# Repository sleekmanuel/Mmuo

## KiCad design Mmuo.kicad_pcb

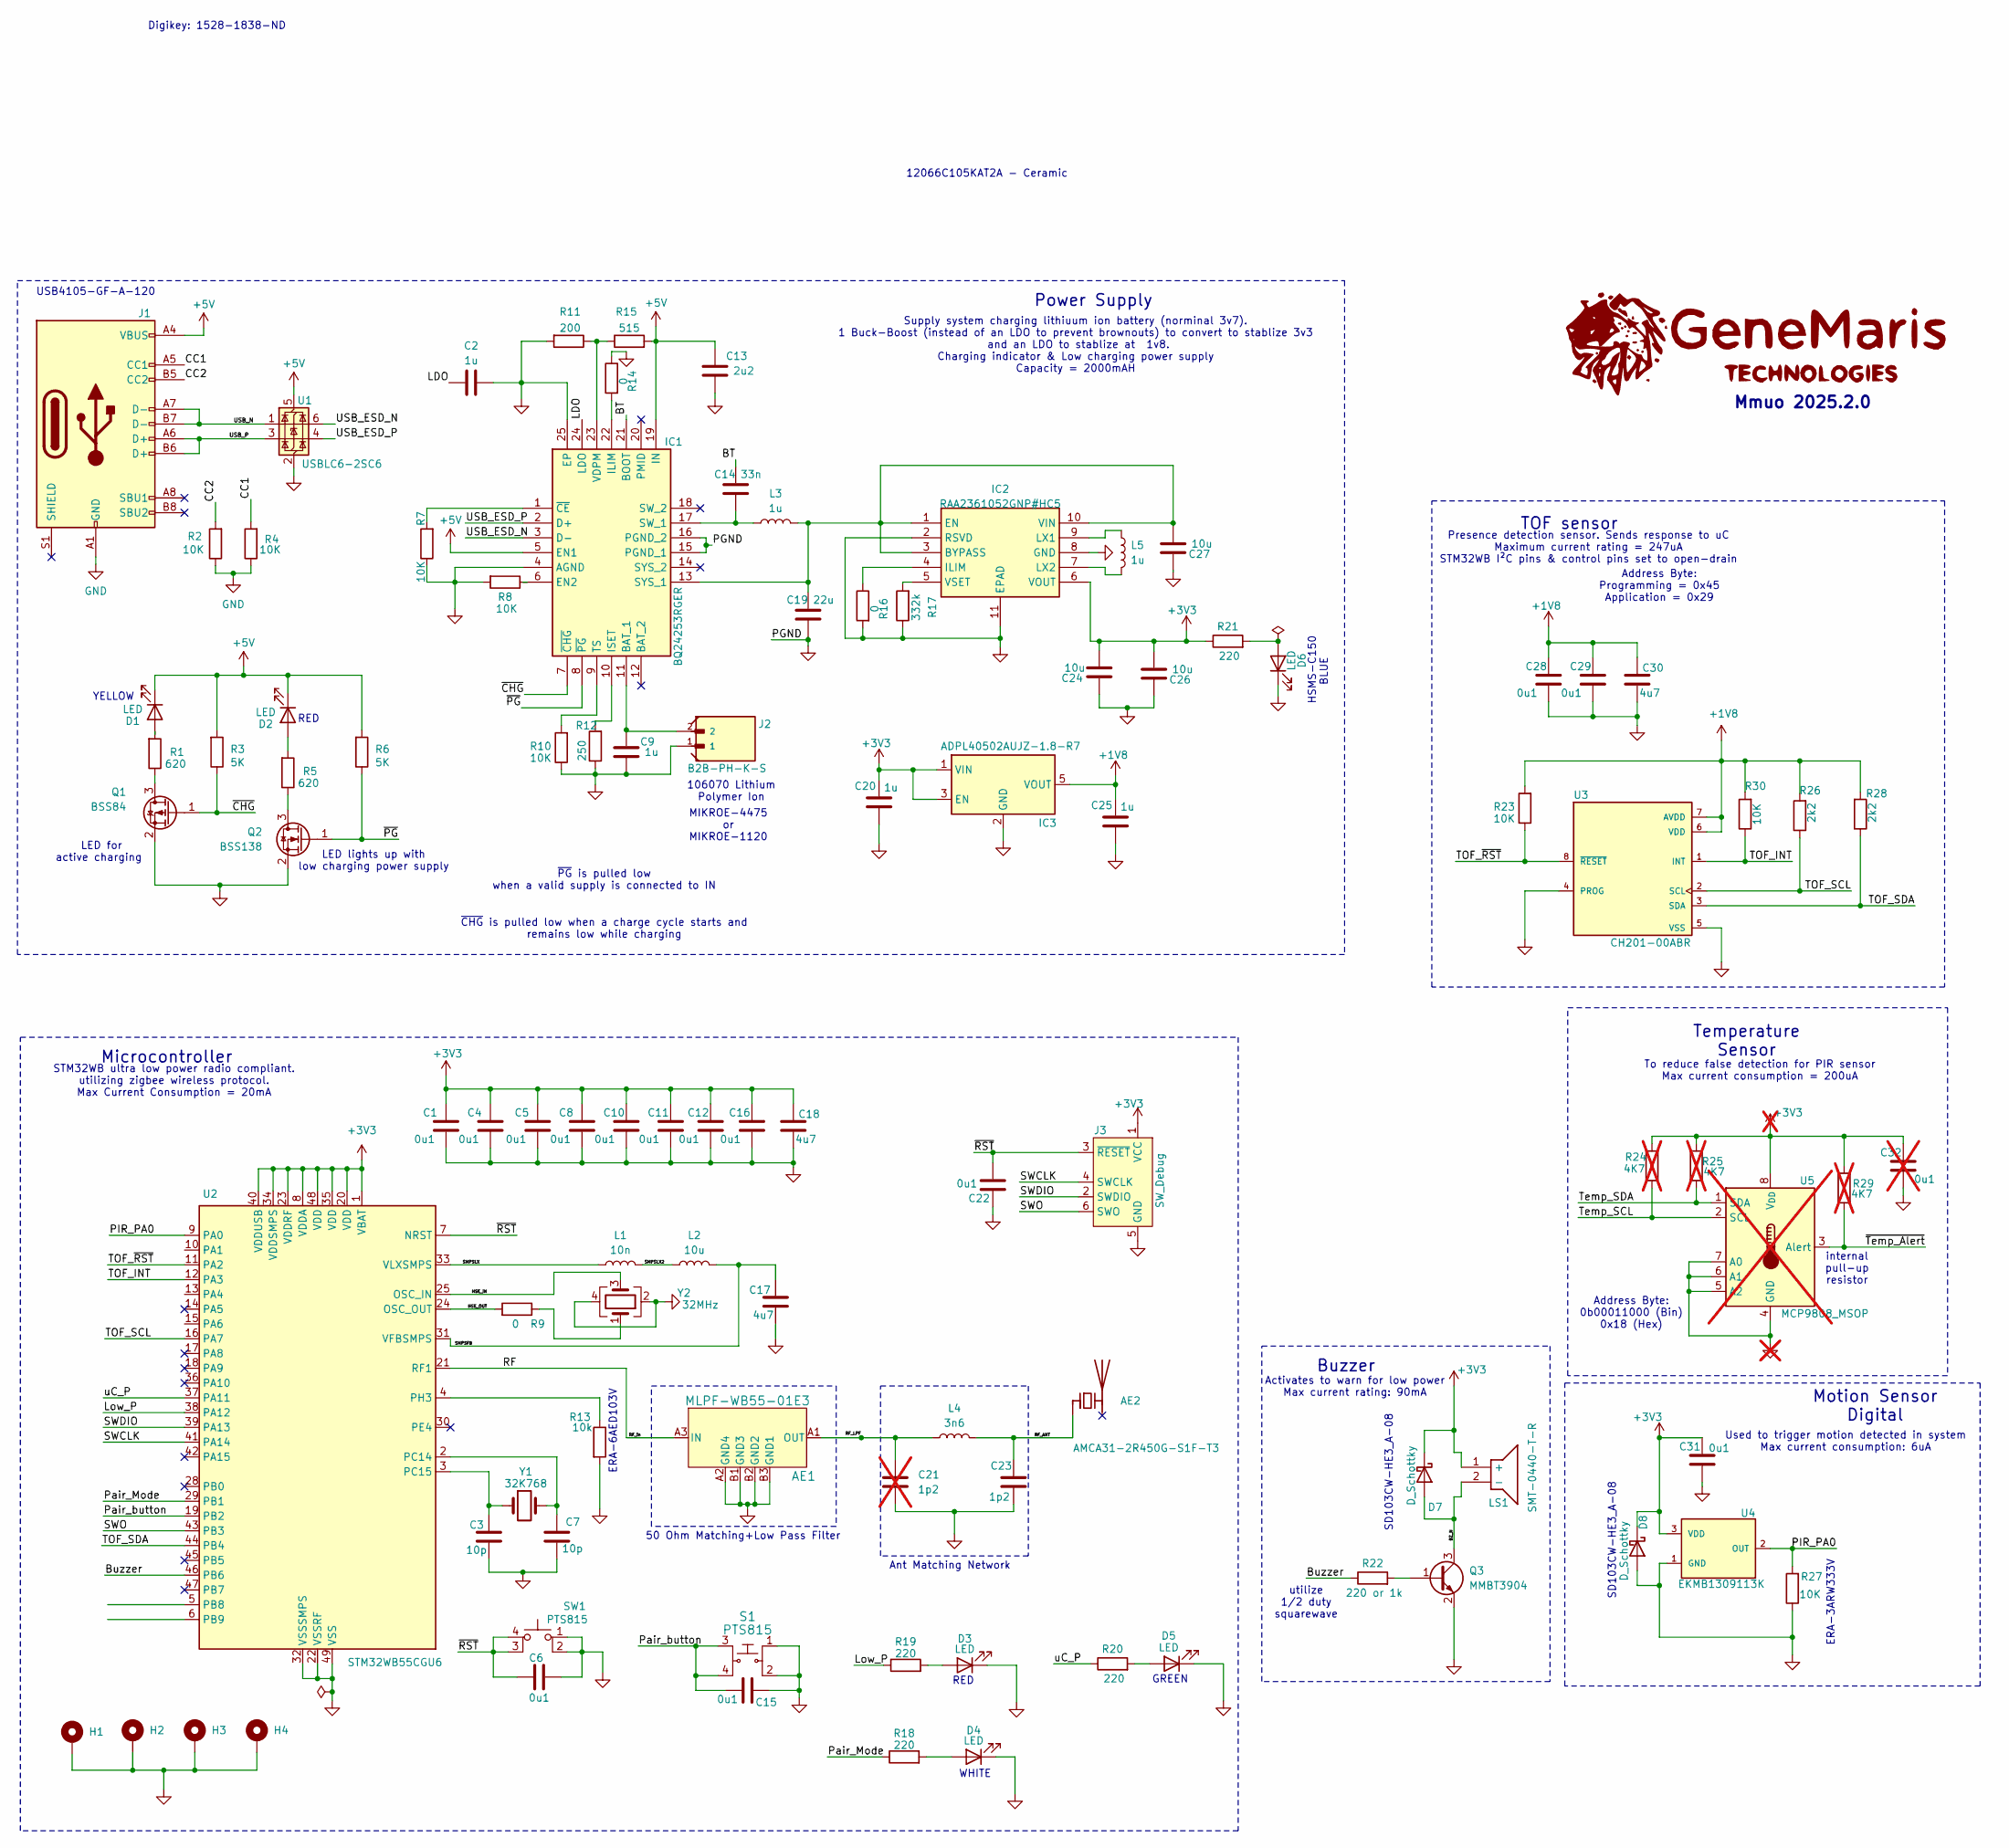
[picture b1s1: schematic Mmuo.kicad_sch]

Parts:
AE1: MLPF-WB55-01E3; MLPF-WB55-01E3_STM
AE2: AMCA31-2R450G-S1F-T3; ANTC3216X140N
C1, C4, C5, C8, C10, C11, C12, C16, C28, C29: 0u1; C_0603_1608Metric_Pad1.08x0.95mm_HandSolder
C2, C9, C20, C25: 1u; C_0603_1608Metric_Pad1.08x0.95mm_HandSolder
C3, C7: 10p; C_0603_1608Metric_Pad1.08x0.95mm_HandSolder
C6: 0u1; C_0603_1608Metric_Pad1.08x0.95mm_HandSolder; JLCPCB Part # C149621
C13: 2u2; C_0603_1608Metric_Pad1.08x0.95mm_HandSolder
C14: 33n; C_0603_1608Metric_Pad1.08x0.95mm_HandSolder
C15, C22, C31: 0u1; C_0603_1608Metric_Pad1.08x0.95mm_HandSolder; Manufacturer_Part_Number 06036C104JAT2A
C17, C18, C30: 4u7; C_0805_2012Metric_Pad1.18x1.45mm_HandSolder
C19: 22u; C_0603_1608Metric_Pad1.08x0.95mm_HandSolder
C21: 1p2; C_0402_1005Metric; not fitted
C23: 1p2; C_0402_1005Metric
C24, C26, C27: 10u; C_0603_1608Metric_Pad1.08x0.95mm_HandSolder
C32: 0u1; C_0603_1608Metric_Pad1.08x0.95mm_HandSolder; Manufacturer_Part_Number 06036C104JAT2A; not fitted
D1, D2, D5, D6: LED; LED_0805_2012Metric_Pad1.15x1.40mm_HandSolder; Manufacturer_Part_Number HSMS-C150; JLCPCB Part# C375580
D3, D4: LED; LED_0805_2012Metric_Pad1.15x1.40mm_HandSolder; Manufacturer_Part_Number HSMD-C150; JLCPCB Part# C62128
D7, D8: D_Schottky; D_SOD-123; Manufacturer_Part_Number SD103CW-HE3_A-08; JLCPCB Part# C2102
H1, H2, H3, H4: MountingHole_Pad; MountingHole_3.5mm_Pad_TopBottom
IC1: BQ24253RGER; QFN50P400X400X100-25N-D; Mouser Part Number 595-BQ24253RGER
IC2: RAA2361052GNP#HC5; SON50P250X250X90-11N-D; Manufacturer_Part_Number RAA2361052GNP#HC5
IC3: ADPL40502AUJZ-1.8-R7; SOT95P280X100-5N; Mouser Part Number 584-ADPL40502AUJZ18R
J1: USB_C_Receptacle_USB2.0_16P; USB_C_Receptacle_GCT_USB4105-xx-A_16P_TopMnt_Horizontal
J2: B2B-PH-K-S; JST_B2B-PH-K-S
J3: SW_Debug; Tag-Connect_TC2030-IDC-FP_2x03_P1.27mm_Vertical
L1: 10n; L_0805_2012Metric_Pad1.05x1.20mm_HandSolder
L2: 10u; L_0805_2012Metric_Pad1.05x1.20mm_HandSolder
L3, L5: 1u; L_0805_2012Metric_Pad1.05x1.20mm_HandSolder
L4: 3n6; L_0402_1005Metric
LS1: SMT-0440-T-R; SMT0440TR; Mouser Part Number 665-SMT-0440-T-R
Q1: BSS84; SOT-23
Q2: BSS138; SOT-23
Q3: MMBT3904; SOT-23
R1, R5: 620; R_0603_1608Metric_Pad0.98x0.95mm_HandSolder; Manufacturer_Part_Number CRCW060310K0FKEI
R2, R4, R7, R8, R27: 10K; R_0805_2012Metric_Pad1.20x1.40mm_HandSolder; Manufacturer_Part_Number CRCW060310K0FKEI
R3, R6: 5K; R_0805_2012Metric_Pad1.20x1.40mm_HandSolder; Manufacturer_Part_Number CRCW060310K0FKEI
R9, R14, R16: 0; R_0603_1608Metric_Pad0.98x0.95mm_HandSolder
R10, R23, R30: 10K; R_0603_1608Metric_Pad0.98x0.95mm_HandSolder; Manufacturer_Part_Number CRCW060310K0FKEI
R11: 200; R_0603_1608Metric_Pad0.98x0.95mm_HandSolder; Manufacturer_Part_Number CRCW060310K0FKEI
R12: 250; R_0603_1608Metric_Pad0.98x0.95mm_HandSolder; Manufacturer_Part_Number CRCW060310K0FKEI
R13: 10k; R_0805_2012Metric_Pad1.20x1.40mm_HandSolder; JLCPCB Part # C3016734
R15: 515; R_0603_1608Metric_Pad0.98x0.95mm_HandSolder; Manufacturer_Part_Number CRCW060310K0FKEI
R17: 332k; R_0603_1608Metric_Pad0.98x0.95mm_HandSolder; Manufacturer_Part_Number CRCW060310K0FKEI
R18, R19, R20, R21: 220; R_0603_1608Metric_Pad0.98x0.95mm_HandSolder; Manufacturer_Part_Number CRCW060310K0FKEI
R22: 220 or 1k; R_0603_1608Metric_Pad0.98x0.95mm_HandSolder; Manufacturer_Part_Number CRCW060310K0FKEI
R24, R25: 4K7; R_0805_2012Metric_Pad1.20x1.40mm_HandSolder; Manufacturer_Part_Number CRCW060310K0FKEI; not fitted
R26, R28: 2k2; R_0603_1608Metric_Pad0.98x0.95mm_HandSolder; Manufacturer_Part_Number CRCW060310K0FKEI
R29: 4K7; R_0603_1608Metric_Pad0.98x0.95mm_HandSolder; Manufacturer_Part_Number CRCW060310K0FKEI; not fitted
S1: PTS815; PTS815SJK250SMTRLFS; MPN TL3315NF160Q; Digi-Key_PN EG4621CT-ND
SW1: PTS815; PTS815SJK250SMTRLFS; JLCPCB Part # C411883
U1: USBLC6-2SC6; SOT-23-6
U2: STM32WB55CGU6; QFN-48-1EP_7x7mm_P0.5mm_EP5.6x5.6mm
U3: CH201-00ABR; XDCR_CH201-00ABR; PARTREV 1.1; DigiKey_Part_Number 1428-CH201-00ABRCT-ND
U4: EKMB1309113K; XDCR_EKMB; Manufacturer_Part_Number EKMB1309113K
U5: MCP9808_MSOP; MSOP-8_3x3mm_P0.65mm; not fitted
Y1: 32K768; Crystal_SMD_2012-2Pin_2.0x1.2mm_HandSoldering
Y2: 32MHz; Crystal_SMD_2016-4Pin_2.0x1.6mm

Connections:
+1V8: C25.1, C28.1, C29.1, C30.1, IC3.5 (VOUT), R23.2, R26.2, R28.2, R30.2, U3.6 (VDD), U3.7 (AVDD)
+3V3: C1.1, C4.1, C5.1, C8.1, C10.1, C11.1, C12.1, C16.1, C18.1, C20.1, C24.1, C26.1, C31.1, C32.1, D7.1 (K), D8.1 (K), IC2.6 (VOUT), IC3.1 (VIN), IC3.3 (EN), J3.1 (VCC), LS1.1 (+), R21.1, R24.2, R25.2, R29.2, U2.1 (VBAT), U2.8 (VDDA), U2.20 (VDD), U2.23 (VDDRF), U2.34 (VDDSMPS), U2.35 (VDD), U2.40 (VDDUSB), U2.48 (VDD), U4.3 (VDD), U5.8 (V_{DD})
+5V: C13.1, D1.1 (K), D2.1 (K), IC1.5 (EN1), IC1.19 (IN), J1.A4 (VBUS), J1.A9 (VBUS), J1.B4 (VBUS), J1.B9 (VBUS), R3.2, R6.2, R15.2, U1.5 (VBUS)
/BT: C14.1, IC1.21 (BOOT)
/BZ_N: D7.2 (A), LS1.2 (-), Q3.3 (C)
/Buzzer: R22.1, U2.46 (PB6)
/CC1: J1.A5 (CC1), R4.2
/CC2: J1.B5 (CC2), R2.2
/HSE_IN: U2.25 (OSC_IN), Y2.3
/HSE_OUT: R9.2, U2.24 (OSC_OUT)
/LDO: C2.1, IC1.24 (LDO)
/Low_P: R19.1, U2.38 (PA12)
/PIR_PA0: R27.2, U2.9 (PA0), U4.2 (OUT)
/Pair_Mode: R18.1, U2.29 (PB1)
/Pair_button: C15.2, S1.3, S1.4, U2.19 (PB2)
/RF: AE1.A3 (IN), U2.21 (RF1)
/RF_ANT: AE2.1 (FEED), C23.1, L4.1
/RF_LPF: AE1.A1 (OUT), C21.1, L4.2
/SMPSFB: C17.1, L2.1, U2.31 (VFBSMPS)
/SMPSLX: L1.2, U2.33 (VLXSMPS)
/SMPSLX2: L1.1, L2.2
/SWCLK: J3.4 (SWCLK), U2.41 (PA14)
/SWDIO: J3.2 (SWDIO), U2.39 (PA13)
/SWO: J3.6 (SWO), U2.43 (PB3)
/TOF_INT: R30.1, U2.12 (PA3), U3.1 (INT)
/TOF_SCL: R26.1, U2.16 (PA7), U3.2 (SCL)
/TOF_SDA: R28.1, U2.44 (PB4), U3.3 (SDA)
/TOF_~RST: R23.1, U2.11 (PA2), U3.8 (~RESET)
/USB_ESD_N: IC1.3 (D-), U1.6 (I/O1)
/USB_ESD_P: IC1.2 (D+), U1.4 (I/O2)
/USB_N: J1.A7 (D-), J1.B7 (D-), U1.1 (I/O1)
/USB_P: J1.A6 (D+), J1.B6 (D+), U1.3 (I/O2)
/uC_P: R20.1, U2.37 (PA11)
/~CHG: IC1.7 (~CHG), Q1.1 (G), R3.1
/~PG: IC1.8 (~PG), Q2.1 (G), R6.1
/~RST: C6.2, C22.2, J3.3 (~RESET), SW1.3 (K), SW1.4 (A), U2.7 (NRST)
GND: AE1.A2 (GND4), AE1.B1 (GND3), AE1.B2 (GND2), AE1.B3 (GND1), C1.2, C2.2, C3.2, C4.2, C5.2, C6.1, C7.2, C8.2, C9.2, C10.2, C11.2, C12.2, C13.2, C15.1, C16.2, C17.2, C18.2, C19.2, C20.2, C21.2, C22.1, C23.2, C24.2, C25.2, C26.2, C27.2, C28.2, C29.2, C30.2, C31.2, C32.2, D3.1 (K), D4.1 (K), D5.1 (K), D6.1 (K), D8.2 (A), H1.1, H2.1, H3.1, H4.1, IC1.4 (AGND), IC1.15 (PGND_1), IC1.16 (PGND_2), IC1.25 (EP), IC2.2 (RSVD), IC2.8 (GND), IC2.11 (EPAD), IC3.2 (GND), J1.A1 (GND), J1.A12 (GND), J1.B1 (GND), J1.B12 (GND), J2.1, J3.5 (GND), Q1.2 (S), Q2.2 (S), Q3.2 (E), R2.1, R4.1, R7.1, R8.2, R10.1, R11.2, R12.1, R13.2, R14.1, R16.2, R17.1, R27.1, S1.1, S1.2, SW1.1, SW1.2, U1.2 (GND), U2.22 (VSSRF), U2.32 (VSSSMPS), U2.49 (VSS), U3.4 (PROG), U3.5 (VSS), U4.1 (GND), U5.4 (GND), U5.5 (A2), U5.6 (A1), U5.7 (A0), Y2.2, Y2.4
unnamed: D1.2 (A), R1.2
unnamed: D2.2 (A), R5.2
unnamed: D3.2 (A), R19.2
unnamed: D4.2 (A), R18.2
unnamed: D5.2 (A), R20.2
unnamed: D6.2 (A), R21.2
unnamed: C9.1, IC1.11 (BAT_1), J2.2
unnamed: IC1.6 (EN2), R8.1
unnamed: IC1.22 (ILIM), R14.2
unnamed: IC1.10 (ISET), R12.2
unnamed: C14.2, IC1.17 (SW_1), L3.1
unnamed: C19.1, C27.1, IC1.13 (SYS_1), IC2.1 (EN), IC2.3 (BYPASS), IC2.10 (VIN), L3.2
unnamed: IC1.9 (TS), R10.2
unnamed: IC1.23 (VDPM), R11.1, R15.1
unnamed: IC1.1 (~CE), R7.2
unnamed: IC2.4 (ILIM), R16.1
unnamed: IC2.9 (LX1), L5.1
unnamed: IC2.7 (LX2), L5.2
unnamed: IC2.5 (VSET), R17.2
unnamed: Q1.3 (D), R1.1
unnamed: Q2.3 (D), R5.1
unnamed: Q3.1 (B), R22.2
unnamed: R9.1, Y2.1
unnamed: R24.1, U5.2 (SCL)
unnamed: R25.1, U5.1 (SDA)
unnamed: R29.1, U5.3 (Alert)
unnamed: C7.1, U2.2 (PC14), Y1.2
unnamed: C3.1, U2.3 (PC15), Y1.1
unnamed: R13.1, U2.4 (PH3)

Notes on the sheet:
RED
Buzzer
YELLOW
Address Byte: 0b00011000 (Bin) 0x18 (Hex)
HSMS-C150
12066C105KAT2A - Ceramic
Motion Sensor Digital
Supply system charging lithiuum ion battery (norminal 3v7). 1 Buck-Boost (instead of an LDO to prevent brownouts) to convert to stablize 3v3 and an LDO to stablize at 1v8. Charging indicator & Low charging power supply Capacity = 2000mAH
Temperature Sensor
Microcontroller
LED lights up with low charging power supply
${TITLE} ${REVISION}
MIKROE-4475 or MIKROE-1120
LED for active charging
GREEN
SD103CW-HE3_A-08
utilize 1/2 duty squarewave
Power Supply
106070 Lithium Polymer Ion
ERA-3ARW333V
Used to trigger motion detected in system Max current consumption: 6uA
STM32WB ultra low power radio compliant. utilizing zigbee wireless protocol. Max Current Consumption = 20mA
Activates to warn for low power Max current rating: 90mA
50 Ohm Matching+Low Pass Filter
Presence detection sensor. Sends response to uC Maximum current rating = 247uA STM32WB I²C pins & control pins set to open-drain
To reduce false detection for PIR sensor Max current consumption = 200uA
~{PG} is pulled low when a valid supply is connected to IN
Ant Matching Network
BLUE
~{CHG} is pulled low when a charge cycle starts and remains low while charging
TOF sensor
internal pull-up resistor
ERA-6AED103V
WHITE
USB4105-GF-A-120
Address Byte: Programming = 0x45 Application = 0x29
Digikey: 1528-1838-ND

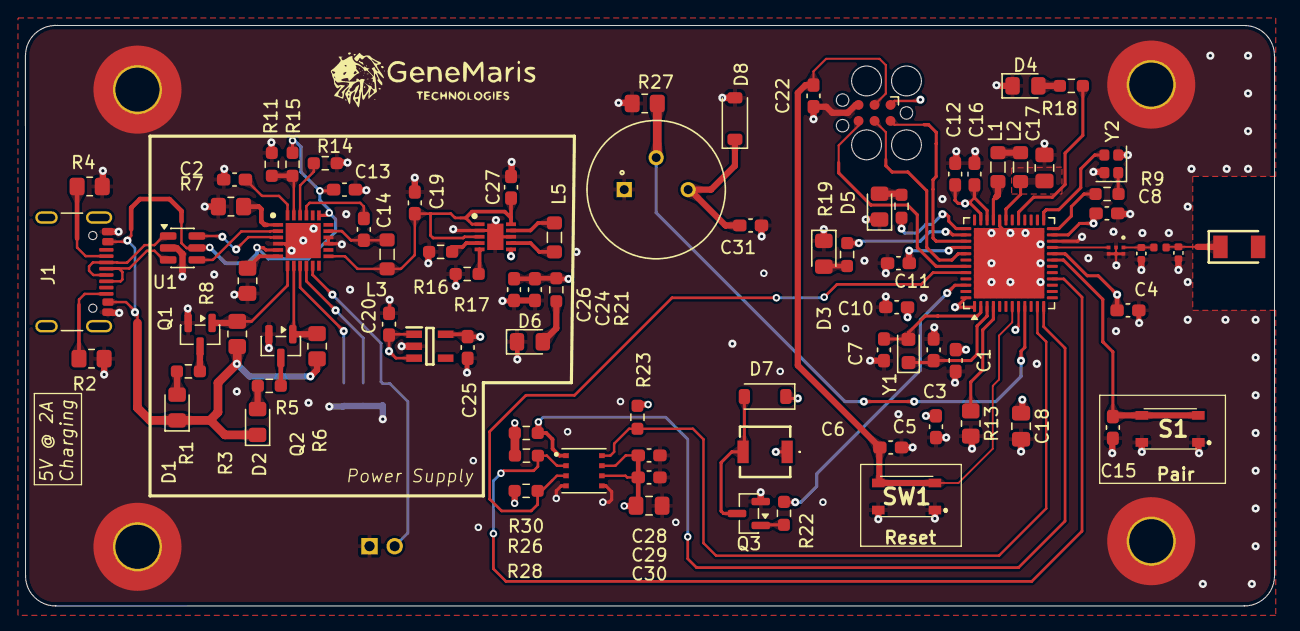
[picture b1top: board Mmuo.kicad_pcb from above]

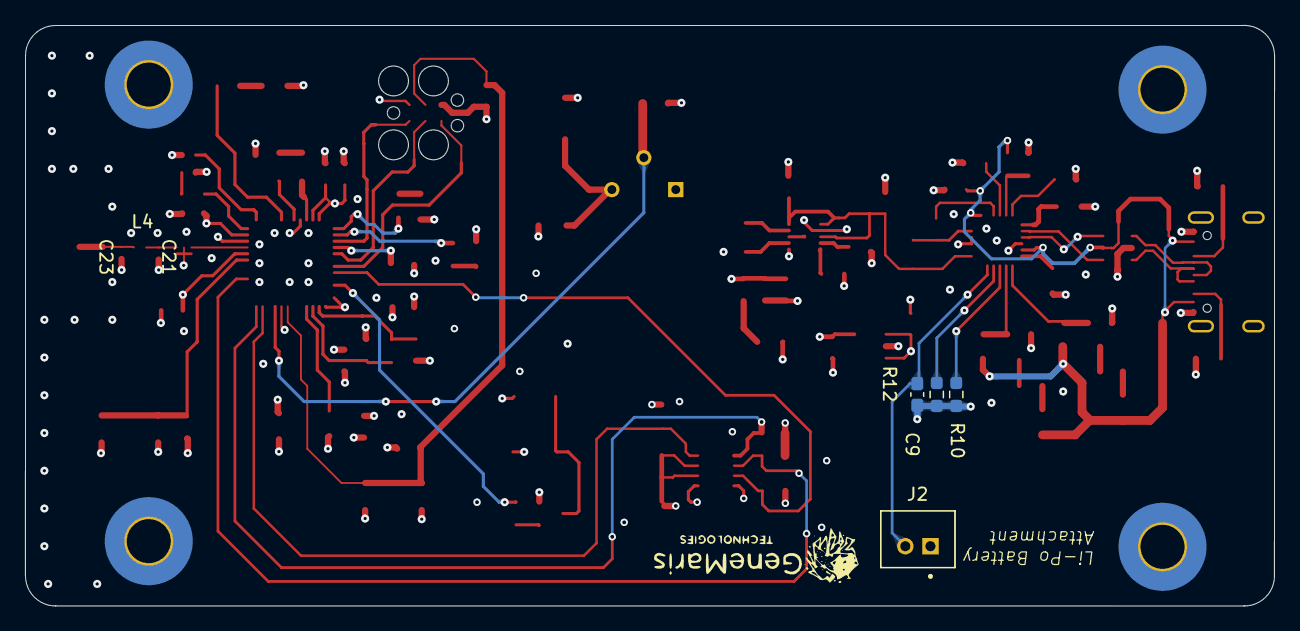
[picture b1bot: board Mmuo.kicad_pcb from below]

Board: 4 copper layers, 99.3 x 46.2 mm, 95 parts (4 on the bottom side), 63 nets.

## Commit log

2025-11-04 Schematics Verifcation
2025-11-19 replacing 3v3 LDO to boost-buck converter
2025-11-19 replaced LDO and rough cut of pcb
2025-11-20 Layout and initial routing
2025-12-12 PCB design and full verification
2025-12-18 min via diameter change to 0.15mm
2025-12-19 V2.0: using a TOF sensor instead of a mmWave sensor
2025-12-22 25_12_22_10
